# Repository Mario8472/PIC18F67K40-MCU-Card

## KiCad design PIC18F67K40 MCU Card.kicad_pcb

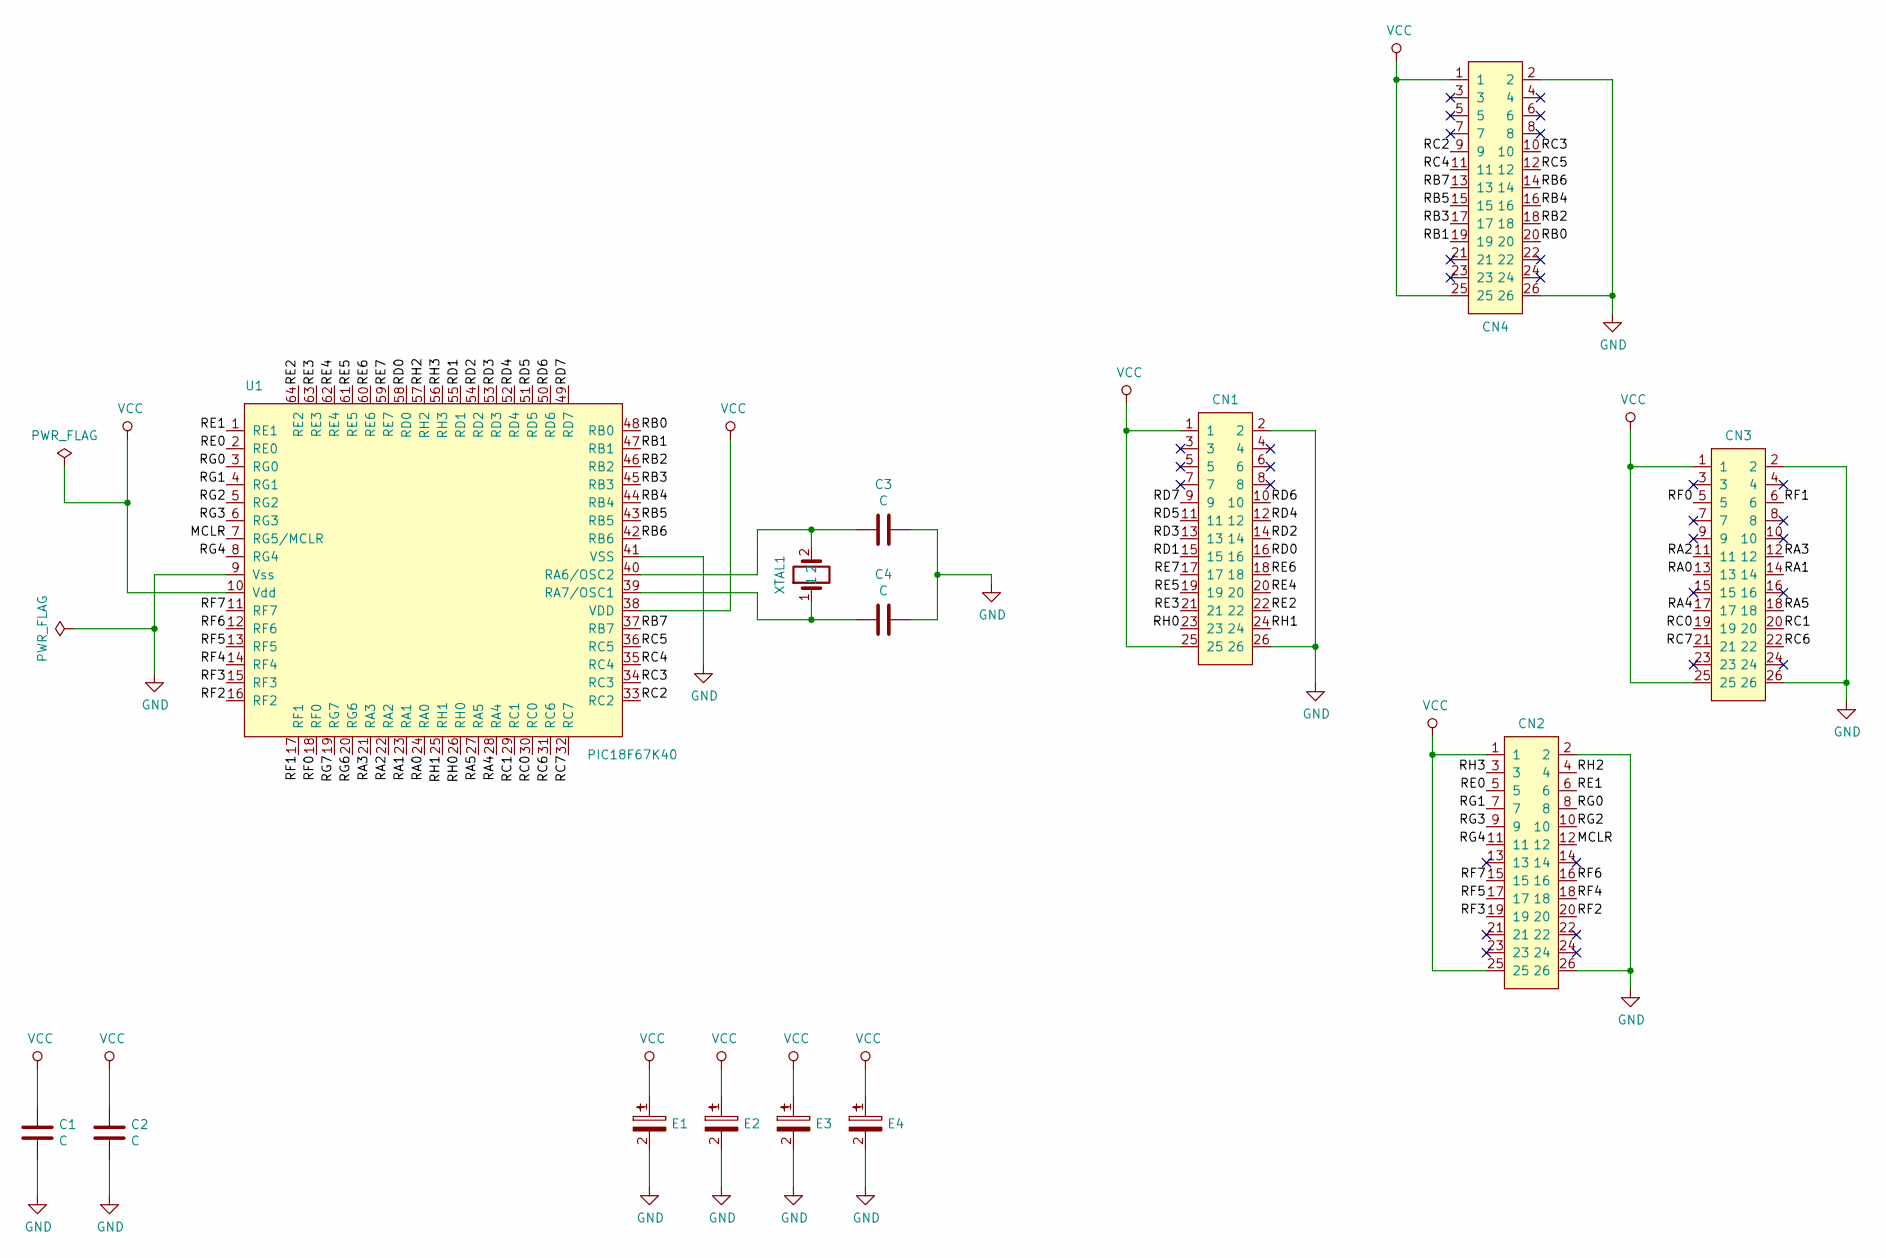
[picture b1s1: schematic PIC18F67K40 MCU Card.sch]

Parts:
C1, C2, C3, C4: C; C_0805_2012Metric
CN1, CN2, CN3, CN4: PinSocket_2x13_2.54mm; SocketPin_2x13_2.54mm
E1, E2, E3, E4: Capacitor_T1206; CAP_TANTALUM
U1: PIC18F67K40; TQFP-64_10x10mm_P0.5mm
XTAL1: QuartzCrystal_SMD; QuartzCrystal_HC49

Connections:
/MCLR: CN2.12, U1.7 (RG5/MCLR)
/RA0: CN3.13, U1.24 (RA0)
/RA1: CN3.14, U1.23 (RA1)
/RA2: CN3.11, U1.22 (RA2)
/RA3: CN3.12, U1.21 (RA3)
/RA4: CN3.17, U1.28 (RA4)
/RA5: CN3.18, U1.27 (RA5)
/RB0: CN4.20, U1.48 (RB0)
/RB1: CN4.19, U1.47 (RB1)
/RB2: CN4.18, U1.46 (RB2)
/RB3: CN4.17, U1.45 (RB3)
/RB4: CN4.16, U1.44 (RB4)
/RB5: CN4.15, U1.43 (RB5)
/RB6: CN4.14, U1.42 (RB6)
/RB7: CN4.13, U1.37 (RB7)
/RC0: CN3.19, U1.30 (RC0)
/RC1: CN3.20, U1.29 (RC1)
/RC2: CN4.9, U1.33 (RC2)
/RC3: CN4.10, U1.34 (RC3)
/RC4: CN4.11, U1.35 (RC4)
/RC5: CN4.12, U1.36 (RC5)
/RC6: CN3.22, U1.31 (RC6)
/RC7: CN3.21, U1.32 (RC7)
/RD0: CN1.16, U1.58 (RD0)
/RD1: CN1.15, U1.55 (RD1)
/RD2: CN1.14, U1.54 (RD2)
/RD3: CN1.13, U1.53 (RD3)
/RD4: CN1.12, U1.52 (RD4)
/RD5: CN1.11, U1.51 (RD5)
/RD6: CN1.10, U1.50 (RD6)
/RD7: CN1.9, U1.49 (RD7)
/RE0: CN2.5, U1.2 (RE0)
/RE1: CN2.6, U1.1 (RE1)
/RE2: CN1.22, U1.64 (RE2)
/RE3: CN1.21, U1.63 (RE3)
/RE4: CN1.20, U1.62 (RE4)
/RE5: CN1.19, U1.61 (RE5)
/RE6: CN1.18, U1.60 (RE6)
/RE7: CN1.17, U1.59 (RE7)
/RF0: CN3.5, U1.18 (RF0)
/RF1: CN3.6, U1.17 (RF1)
/RF2: CN2.20, U1.16 (RF2)
/RF3: CN2.19, U1.15 (RF3)
/RF4: CN2.18, U1.14 (RF4)
/RF5: CN2.17, U1.13 (RF5)
/RF6: CN2.16, U1.12 (RF6)
/RF7: CN2.15, U1.11 (RF7)
/RG0: CN2.8, U1.3 (RG0)
/RG1: CN2.7, U1.4 (RG1)
/RG2: CN2.10, U1.5 (RG2)
/RG3: CN2.9, U1.6 (RG3)
/RG4: CN2.11, U1.8 (RG4)
/RG6: U1.20 (RG6)
/RG7: U1.19 (RG7)
/RH0: CN1.23, U1.26 (RH0)
/RH1: CN1.24, U1.25 (RH1)
/RH2: CN2.4, U1.57 (RH2)
/RH3: CN2.3, U1.56 (RH3)
GND: C1.2, C2.2, C3.2, C4.2, CN1.2, CN1.26, CN2.2, CN2.26, CN3.2, CN3.26, CN4.2, CN4.26, E1.2, E2.2, E3.2, E4.2, U1.9 (Vss), U1.41 (VSS)
unnamed: C3.1, U1.40 (RA6/OSC2), XTAL1.2
unnamed: C4.1, U1.39 (RA7/OSC1), XTAL1.1
VCC: C1.1, C2.1, CN1.1, CN1.25, CN2.1, CN2.25, CN3.1, CN3.25, CN4.1, CN4.25, E1.1, E2.1, E3.1, E4.1, U1.10 (Vdd), U1.38 (VDD)

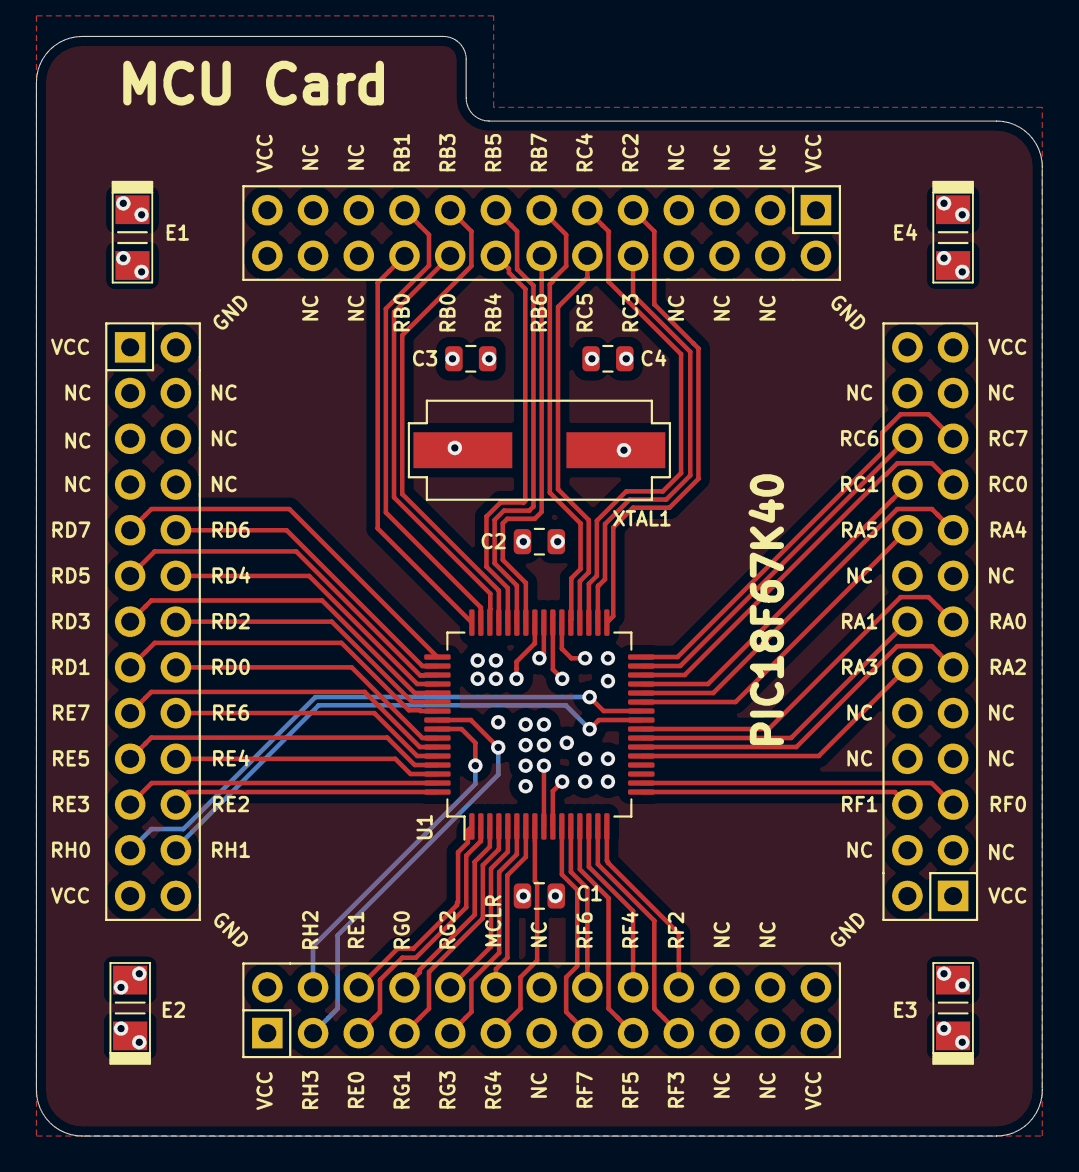
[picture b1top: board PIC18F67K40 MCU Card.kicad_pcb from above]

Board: 4 copper layers, 55.9 x 61.1 mm, 14 parts (0 on the bottom side), 60 nets.
